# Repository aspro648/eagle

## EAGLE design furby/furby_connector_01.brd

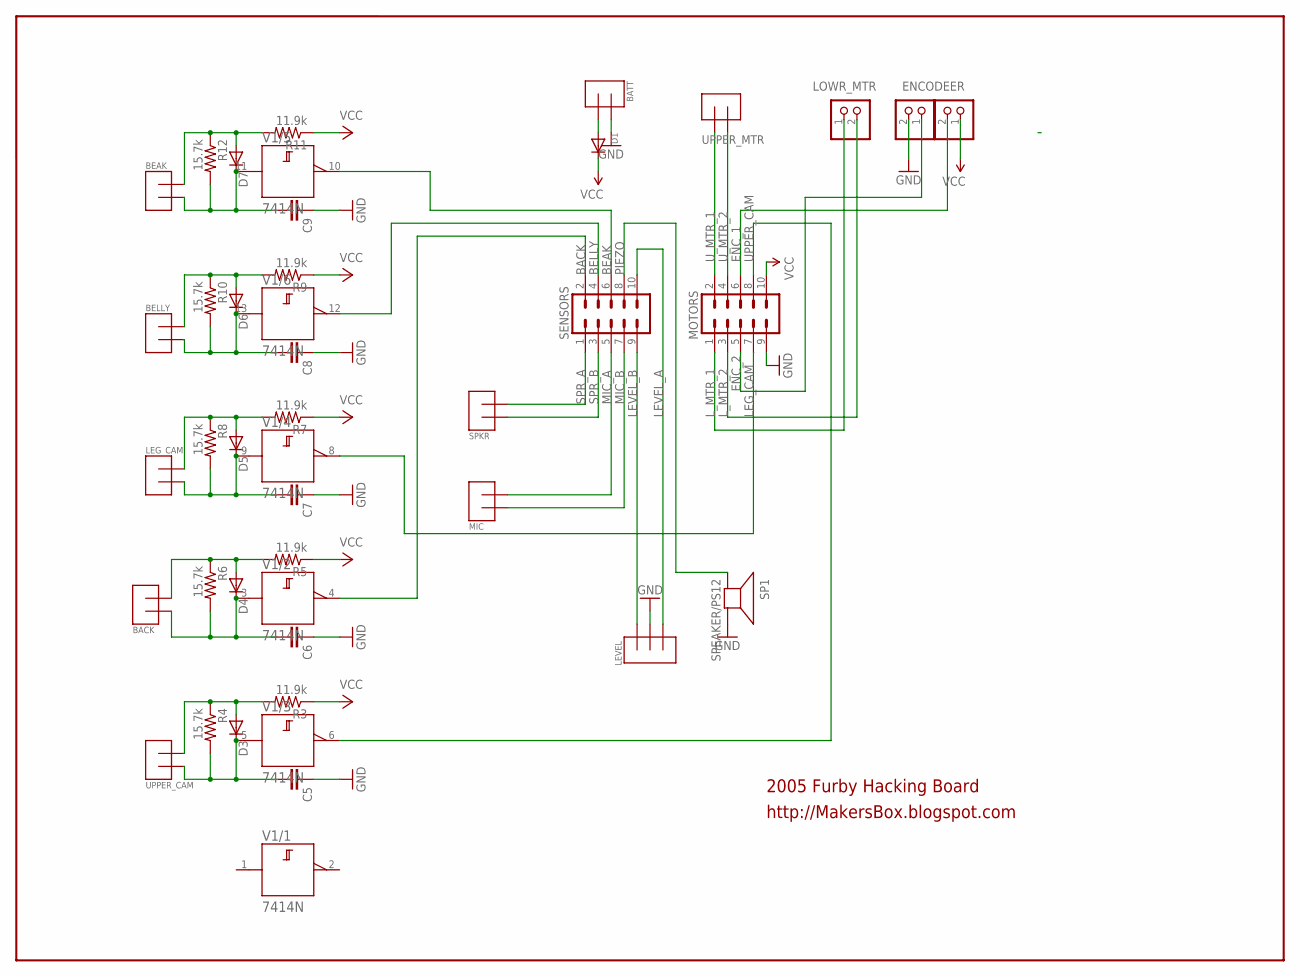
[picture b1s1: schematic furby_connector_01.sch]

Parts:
BACK: TERMINAL2; TERMINAL_2
BATT: TERMINAL2; TERMINAL_2
BEAK: TERMINAL2; TERMINAL_2
BELLY: TERMINAL2; TERMINAL_2
C5, C6, C7, C8, C9: CAPPTH; CAP-PTH-SMALL
D1: DIODEDO-1N4148; DO-1N4148
D3, D4, D5, D6, D7: DIODE-D-2.5; D-2.5
ENCODE2: JST_2PIN-THM; JST-PH-2-THM
ENCODEER: JST_2PIN-THM; JST-PH-2-THM
LEG_CAM: TERMINAL2; TERMINAL_2
LEVEL: TERMINAL; TERMINAL_3
LOWR_MTR: JST_2PIN-THM; JST-PH-2-THM
MIC: TERMINAL2; TERMINAL_2
MOTORS: M05X2SHD; 2X5-SHROUDED
R3, R5, R7, R9, R11: 11.9k; 0204V
R4, R6, R8, R10, R12: 15.7k; 0204V
SENSORS: M05X2SHD; 2X5-SHROUDED
SP1: SPEAKER/PS12; PS12
SPKR: TERMINAL2; TERMINAL_2
UPPER_CAM: TERMINAL2; TERMINAL_2
UPPER_MTR: TERMINAL2; TERMINAL_2
V1: 7414N; DIL14

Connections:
+UB: V1.14 (+UB)
-UB: V1.7 (-UB)
BACK: SENSORS.2, V1.4 (Y)
BEAK: SENSORS.6, V1.10 (Y)
BELLY: SENSORS.4, V1.12 (Y)
ENC_1: ENCODE2.2 (1), MOTORS.6
ENC_2: ENCODEER.1 (2), MOTORS.5
GND: BATT.P$1, C5.1, C6.1, C7.1, C8.1, C9.1, ENCODEER.2 (1), LEVEL.P$2, MOTORS.9, SP1.P$2 (-)
LEG_CAM: MOTORS.7, V1.8 (Y)
LEVEL_A: LEVEL.P$3, SENSORS.10
LEVEL_B: LEVEL.P$1, SENSORS.9
L_MTR_1: LOWR_MTR.1 (2), MOTORS.1
L_MTR_2: LOWR_MTR.2 (1), MOTORS.3
MIC_A: MIC.P$2, SENSORS.5
MIC_B: MIC.P$1, SENSORS.7
unnamed: BATT.P$2, D1.A
unnamed: D3.A, R3.2, R4.1, UPPER_CAM.P$2
unnamed: C5.2, D3.C, R4.2, UPPER_CAM.P$1, V1.5 (A)
unnamed: BACK.P$2, D4.A, R5.2, R6.1
unnamed: BACK.P$1, C6.2, D4.C, R6.2, V1.3 (A)
unnamed: D5.A, LEG_CAM.P$1, R7.2, R8.1
unnamed: C7.2, D5.C, LEG_CAM.P$2, R8.2, V1.9 (A)
unnamed: BELLY.P$1, D6.A, R9.2, R10.1
unnamed: BELLY.P$2, C8.2, D6.C, R10.2, V1.13 (A)
unnamed: BEAK.P$1, D7.A, R11.2, R12.1
unnamed: BEAK.P$2, C9.2, D7.C, R12.2, V1.11 (A)
PIEZO: SENSORS.8, SP1.P$1 (+)
SPR_A: SENSORS.1, SPKR.P$2
SPR_B: SENSORS.3, SPKR.P$1
UPPER_CAM: MOTORS.8, V1.6 (Y)
U_MTR_1: MOTORS.2, UPPER_MTR.P$1
U_MTR_2: MOTORS.4, UPPER_MTR.P$2
VCC: D1.C, ENCODE2.1 (2), MOTORS.10, R3.1, R5.1, R7.1, R9.1, R11.1

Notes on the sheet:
2005 Furby Hacking Board
http://MakersBox.blogspot.com

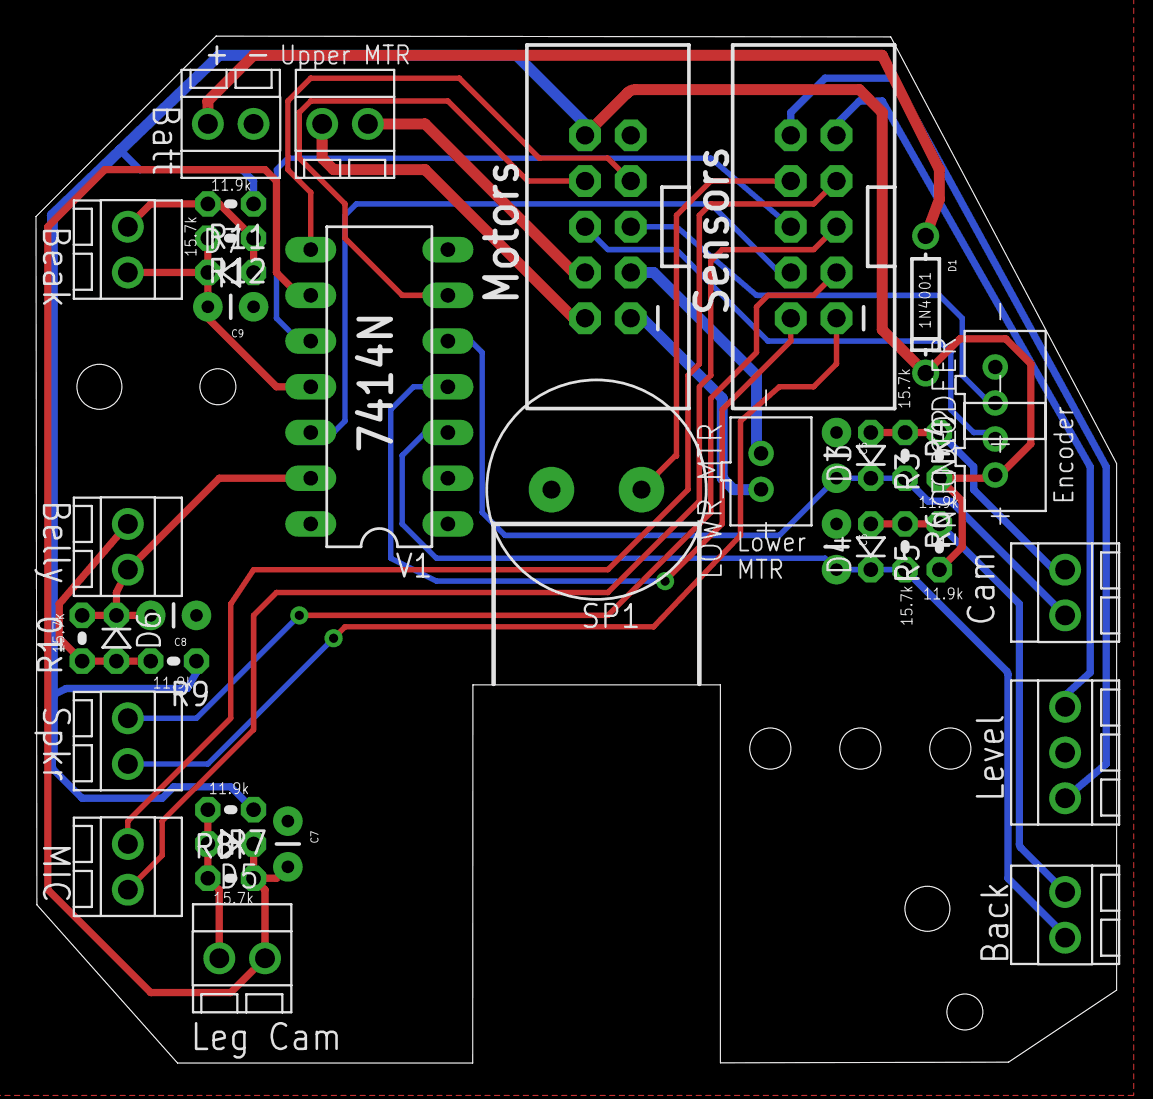
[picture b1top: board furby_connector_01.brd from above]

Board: 2 copper layers, 60.0 x 57.1 mm, 38 parts (0 on the bottom side), 31 nets.

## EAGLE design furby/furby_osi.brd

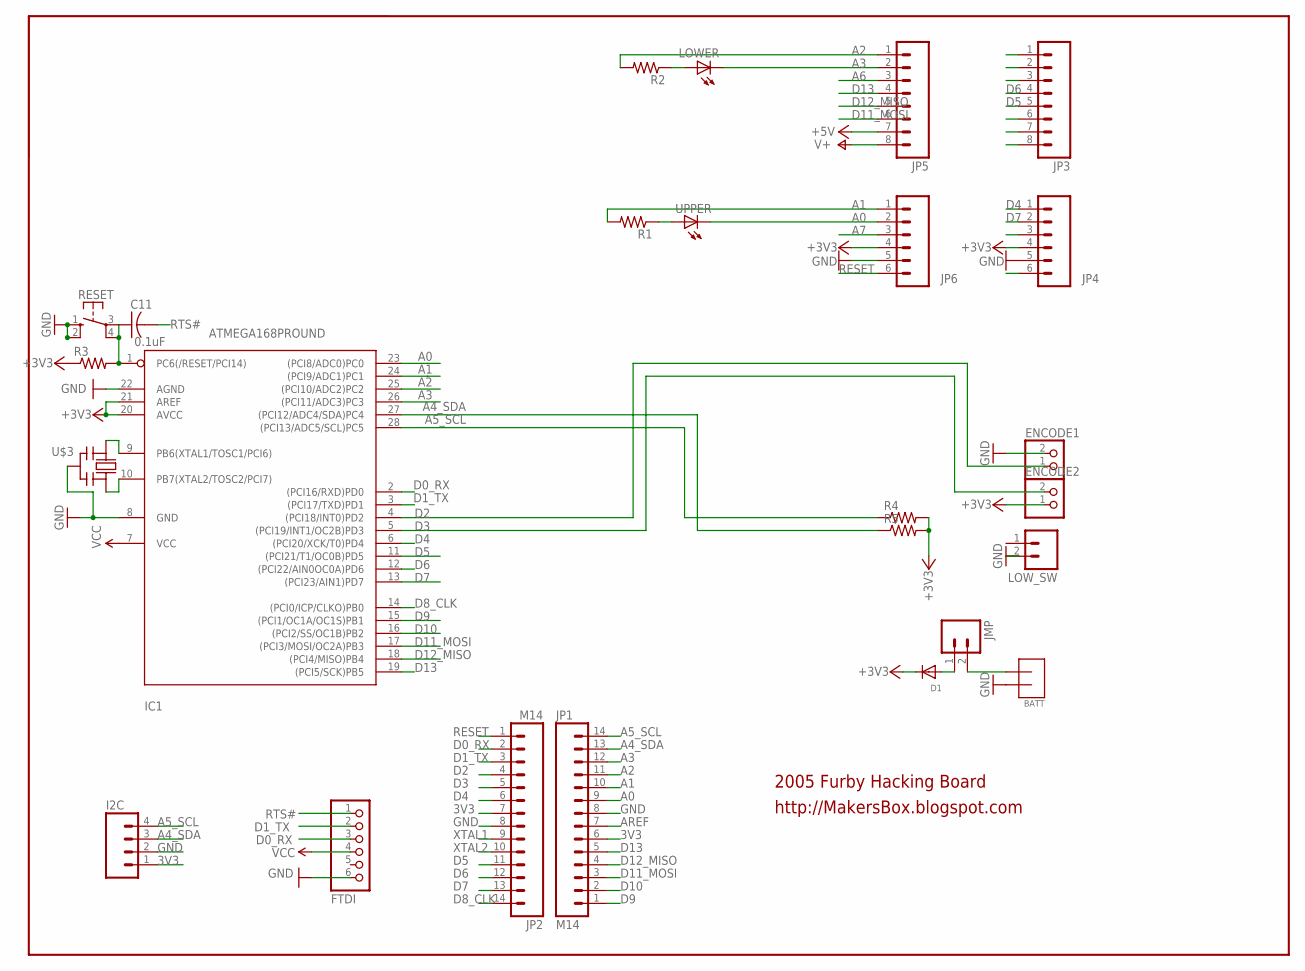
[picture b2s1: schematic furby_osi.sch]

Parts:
BATT: TERMINAL2; TERMINAL_2
C11: 0.1uF; C025-025X050
D1: DIODEDO-1N4148; DO-1N4148
ENCODE1, ENCODE2: JST_2PIN-THM; JST-PH-2-THM
FTDI: FTDI; 1X06-CLEANBIG
I2C: M04PTH; 1X04
IC1: ATMEGA168PROUND; DIL28-3-ROUND
JMP: M02PTH; 1X02
JP1, JP2: M14; 1X14
JP3, JP5: M081X08; 1X08
JP4, JP6: M06SIP; 1X06
LOWER: LED3MM
LOW_SW: M02PTH; 1X02
R1, R2, R3, R4, R5: R-US_0204/7; 0204/7
RESET: 10-XX; B3F-10XX
U$3: CERMOSCILL-THM; CERM_OSC
UPPER: LED3MM

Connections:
3V3: D1.C, ENCODE2.1 (2), FTDI.4, I2C.1, IC1.7 (VCC), IC1.20 (AVCC), IC1.21 (AREF), JP1.6, JP2.7, JP4.4, JP6.4, R3.1, R4.2, R5.2
+5V: JP5.7
A0: IC1.23 ((PCI8/ADC0)PC0), JP1.9, JP6.2, UPPER.K (C)
A1: IC1.24 ((PCI9/ADC1)PC1), JP1.10, JP6.1, R1.2
A2: IC1.25 ((PCI10/ADC2)PC2), JP1.11, JP5.1, R2.2
A3: IC1.26 ((PCI11/ADC3)PC3), JP1.12, JP5.2, LOWER.K (C)
A4_SDA: I2C.3, IC1.27 ((PCI12/ADC4/SDA)PC4), JP1.13, R5.1
A5_SCL: I2C.4, IC1.28 ((PCI13/ADC5/SCL)PC5), JP1.14, R4.1
A6: JP5.3
A7: JP6.3
AREF: JP1.7
D0_RX: FTDI.3, IC1.2 ((PCI16/RXD)PD0), JP2.2
D1_TX: FTDI.2, IC1.3 ((PCI17/TXD)PD1), JP2.3
D2: ENCODE1.1 (2), IC1.4 ((PCI18/INT0)PD2), JP2.4
D3: ENCODE2.2 (1), IC1.5 ((PCI19/INT1/OC2B)PD3), JP2.5
D4: IC1.6 ((PCI20/XCK/T0)PD4), JP2.6, JP4.1
D5: IC1.11 ((PCI21/T1/OC0B)PD5), JP2.11, JP3.5
D6: IC1.12 ((PCI22/AIN0OC0A)PD6), JP2.12, JP3.4
D7: IC1.13 ((PCI23/AIN1)PD7), JP2.13, JP4.2
D8_CLK: IC1.14 ((PCI0/ICP/CLKO)PB0), JP2.14
D9: IC1.15 ((PCI1/OC1A/OC1S)PB1), JP1.1
D10: IC1.16 ((PCI2/SS/OC1B)PB2), JP1.2
D11_MOSI: IC1.17 ((PCI3/MOSI/OC2A)PB3), JP1.3, JP5.6
D12_MISO: IC1.18 ((PCI4/MISO)PB4), JP1.4, JP5.5
D13: IC1.19 ((PCI5/SCK)PB5), JP1.5, JP5.4
GND: BATT.P$1, ENCODE1.2 (1), FTDI.6, I2C.2, IC1.8 (GND), IC1.22 (AGND), JP1.8, JP2.8, JP4.5, JP6.5, LOW_SW.2, RESET.1 (S), RESET.2 (S1), U$3.P$2 (GND)
unnamed: R1.1, UPPER.A
unnamed: LOWER.A, R2.1
unnamed: BATT.P$2, JMP.2
unnamed: D1.A, JMP.1
RESET: C11.1, IC1.1 (PC6(/RESET/PCI14)), JP2.1, JP6.6, R3.2, RESET.3, RESET.4 (P1)
RTS#: C11.2, FTDI.1
V+: JP5.8
XTAL1: IC1.9 (PB6(XTAL1/TOSC1/PCI6)), JP2.9, U$3.P$1 (IN)
XTAL2: IC1.10 (PB7(XTAL2/TOSC2/PCI7)), JP2.10, U$3.P$3 (OUT)

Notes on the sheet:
2005 Furby Hacking Board
http://MakersBox.blogspot.com

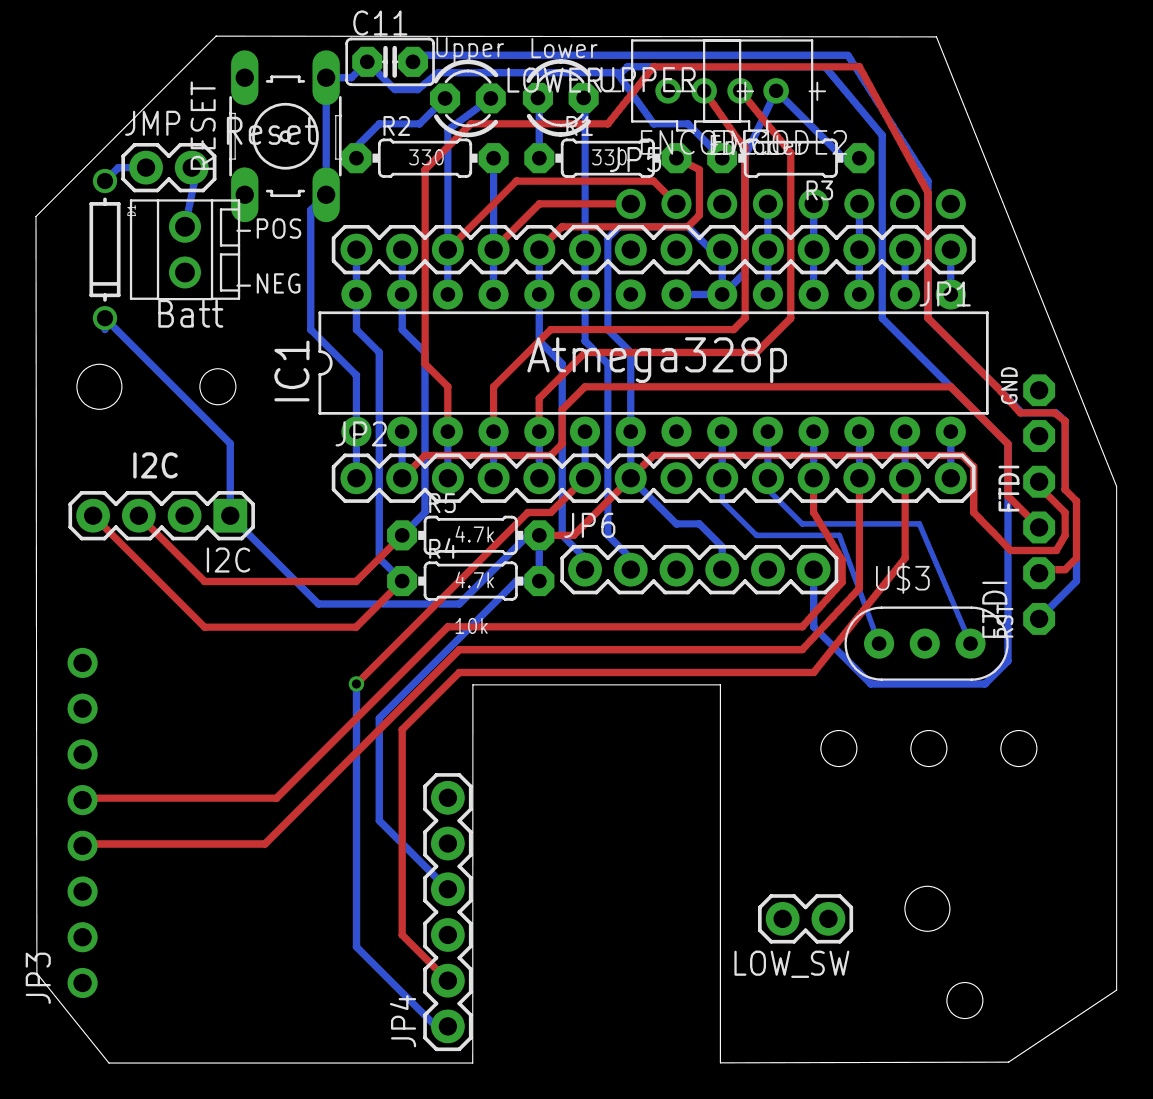
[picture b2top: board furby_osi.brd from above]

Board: 2 copper layers, 60.0 x 57.1 mm, 25 parts (0 on the bottom side), 30 nets.

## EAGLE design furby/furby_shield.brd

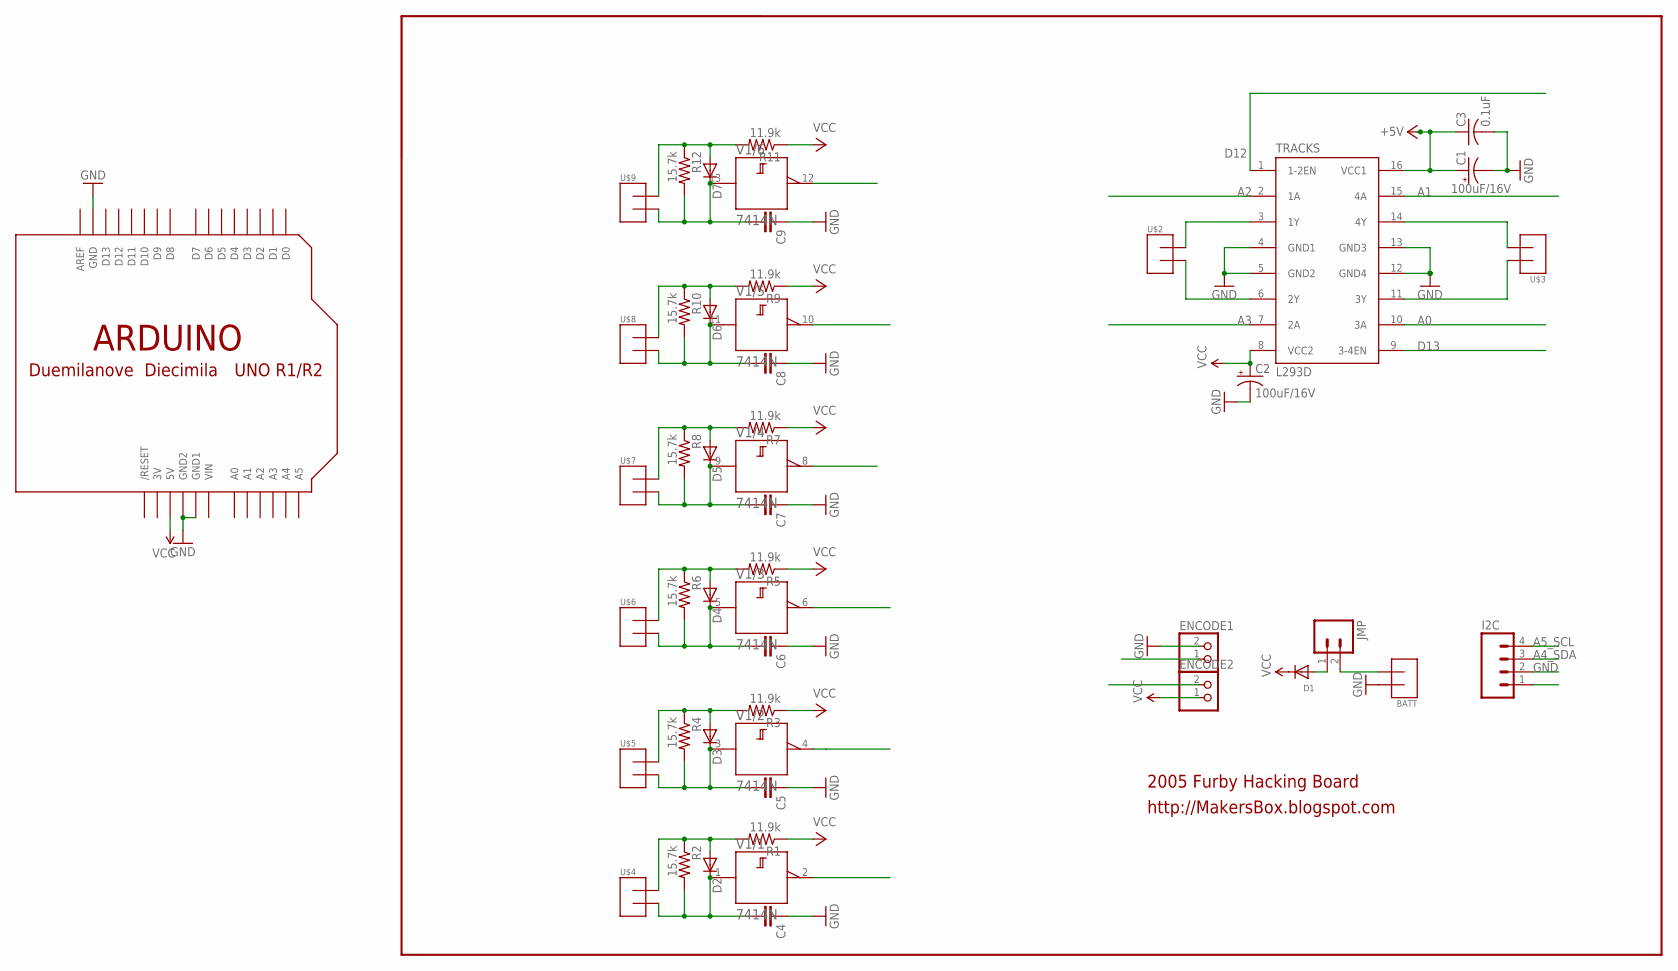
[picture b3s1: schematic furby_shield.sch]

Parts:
BATT: TERMINAL2; TERMINAL_2
C1, C2: 100uF/16V; E2,5-6
C3: 0.1uF; C025-025X050
C4, C5, C6, C7, C8, C9: CAPPTH; CAP-PTH-SMALL
D1: DIODEDO-1N4148; DO-1N4148
D2, D3, D4, D5, D6, D7: DIODE-D-2.5; D-2.5
ENCODE1, ENCODE2: JST_2PIN-THM; JST-PH-2-THM
I2C: M04PTH; 1X04
JMP: M02PTH; 1X02
R1, R3, R5, R7, R9, R11: 11.9k; 0204V
R2, R4, R6, R8, R10, R12: 15.7k; 0204V
TRACKS: L293D; DIL16
U$1: ARDUINO-BPLACE
U$2, U$3, U$4, U$5, U$6, U$7, U$8, U$9: TERMINAL2; TERMINAL_2
V1: 7414N; DIL14

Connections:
3V: U$1.3V
+5V: C1.+, C3.1, TRACKS.16 (VCC1)
+UB: V1.14 (+UB)
-UB: V1.7 (-UB)
A0: TRACKS.10 (3A)
A1: TRACKS.15 (4A)
A2: TRACKS.2 (1A)
A3: TRACKS.7 (2A)
A4: V1.2 (Y)
A4_SDA: I2C.3
A5: V1.8 (Y)
A5_SCL: I2C.4
A6: V1.12 (Y)
D1: V1.4 (Y)
D2: V1.6 (Y)
D3: V1.10 (Y)
D12: TRACKS.1 (1-2EN)
D13: TRACKS.9 (3-4EN)
GND: BATT.P$1, C1.-, C2.-, C3.2, C4.1, C5.1, C6.1, C7.1, C8.1, C9.1, ENCODE1.2 (1), I2C.2, TRACKS.4 (GND1), TRACKS.5 (GND2), TRACKS.12 (GND4), TRACKS.13 (GND3), U$1.GND, U$1.GND1, U$1.GND2
unnamed: BATT.P$2, JMP.2
unnamed: D1.A, JMP.1
unnamed: TRACKS.6 (2Y), U$2.P$2
unnamed: TRACKS.11 (3Y), U$3.P$1
unnamed: TRACKS.14 (4Y), U$3.P$2
unnamed: TRACKS.3 (1Y), U$2.P$1
unnamed: D2.A, R1.2, R2.1, U$4.P$1
unnamed: C4.2, D2.C, R2.2, U$4.P$2, V1.1 (A)
unnamed: D3.A, R3.2, R4.1, U$5.P$1
unnamed: C5.2, D3.C, R4.2, U$5.P$2, V1.3 (A)
unnamed: D4.A, R5.2, R6.1, U$6.P$1
unnamed: C6.2, D4.C, R6.2, U$6.P$2, V1.5 (A)
unnamed: D5.A, R7.2, R8.1, U$7.P$1
unnamed: C7.2, D5.C, R8.2, U$7.P$2, V1.9 (A)
unnamed: D6.A, R9.2, R10.1, U$8.P$1
unnamed: C8.2, D6.C, R10.2, U$8.P$2, V1.11 (A)
unnamed: D7.A, R11.2, R12.1, U$9.P$1
unnamed: C9.2, D7.C, R12.2, U$9.P$2, V1.13 (A)
VCC: C2.+, D1.C, ENCODE2.1 (2), R1.1, R3.1, R5.1, R7.1, R9.1, R11.1, TRACKS.8 (VCC2), U$1.5V
VIN: U$1.VIN

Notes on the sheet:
2005 Furby Hacking Board
http://MakersBox.blogspot.com

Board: 2 copper layers, 44 parts (0 on the bottom side), 21 nets, no tracks yet.

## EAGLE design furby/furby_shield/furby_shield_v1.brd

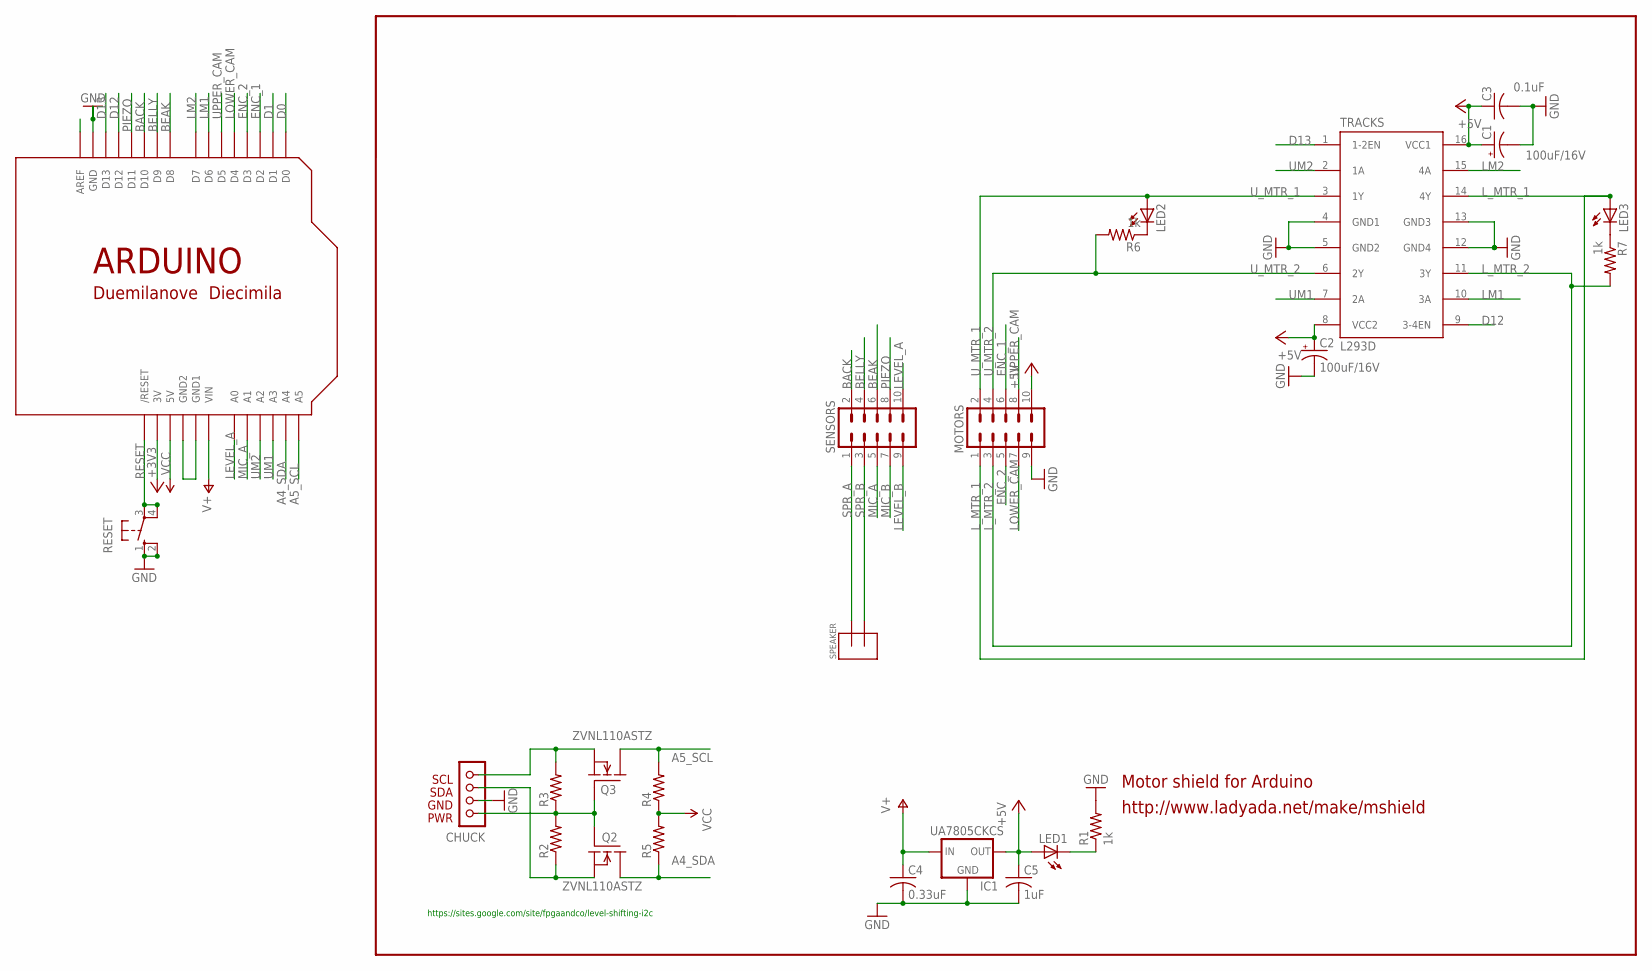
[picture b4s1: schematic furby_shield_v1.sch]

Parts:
C1, C2: 100uF/16V; E2,5-6
C3: 0.1uF; C025-025X050
C4: 0.33uF; C025-024X044
C5: 1uF; C025-024X044
CHUCK: NUNCHUCK; CONN
IC1: UA7805CKCS; TO-220-ALT
LED1, LED2, LED3: LED3MM
MOTORS: M05X2SHD; 2X5-SHROUDED
Q2, Q3: ZVNL110ASTZ; TO92-INLINE
R1, R6, R7: 1k; 0204/5
R2, R3, R4, R5: R-US_0204/7; 0204/7
RESET: 10-XX; B3F-10XX
SENSORS: M05X2SHD; 2X5-SHROUDED
SPEAKER: TERMINAL2; TERMINAL_2
TRACKS: L293D; DIL16
U$1: ARDUINO-NOHOLE

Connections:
+3V3: CHUCK.PWR, Q2.2 (G), Q3.2 (G), R2.2, R3.1, U$1.3V
+5V: C1.+, C2.+, C3.1, C5.1, IC1.OUT, LED1.A, MOTORS.10, TRACKS.8 (VCC2), TRACKS.16 (VCC1)
A4_SDA: Q2.1 (D), R5.1, U$1.A4
A5_SCL: Q3.1 (D), R4.2, U$1.A5
BACK: SENSORS.2, U$1.D10
BEAK: SENSORS.6, U$1.D8
BELLY: SENSORS.4, U$1.D9
D0: U$1.D0
D1: U$1.D1
D12: TRACKS.9 (3-4EN), U$1.D12
D13: TRACKS.1 (1-2EN), U$1.D13
ENC_1: MOTORS.6, U$1.D2
ENC_2: MOTORS.5, U$1.D3
GND: C1.-, C2.-, C3.2, C4.2, C5.2, CHUCK.GND, IC1.GND, MOTORS.9, R1.2, RESET.1 (S), RESET.2 (S1), TRACKS.4 (GND1), TRACKS.5 (GND2), TRACKS.12 (GND4), TRACKS.13 (GND3), U$1.GND, U$1.GND1, U$1.GND2
LEVEL_A: SENSORS.10, U$1.A0
LEVEL_B: SENSORS.9
LM1: TRACKS.10 (3A), U$1.D6
LM2: TRACKS.15 (4A), U$1.D7
LOWER_CAM: MOTORS.7, U$1.D4
L_MTR_1: LED3.A, MOTORS.1, TRACKS.14 (4Y)
L_MTR_2: MOTORS.3, R7.2, TRACKS.11 (3Y)
MIC_A: SENSORS.5, U$1.A1
MIC_B: SENSORS.7
unnamed: LED2.K (C), R6.1
unnamed: LED1.K (C), R1.1
unnamed: LED3.K (C), R7.1
PIEZO: SENSORS.8, U$1.D11
RESET: RESET.3, RESET.4 (P1), U$1.RESET (/RESET)
SCL: CHUCK.SCL, Q3.3 (S), R3.2
SDA: CHUCK.SDA, Q2.3 (S), R2.1
SPR_A: SENSORS.1, SPEAKER.P$1
SPR_B: SENSORS.3, SPEAKER.P$2
UM1: TRACKS.7 (2A), U$1.A3
UM2: TRACKS.2 (1A), U$1.A2
UPPER_CAM: MOTORS.8, U$1.D5
U_MTR_1: LED2.A, MOTORS.2, TRACKS.3 (1Y)
U_MTR_2: MOTORS.4, R6.2, TRACKS.6 (2Y)
V+: C4.1, IC1.IN, U$1.VIN
VCC: R4.1, R5.2, U$1.5V, U$1.AREF

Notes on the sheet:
Motor shield for Arduino
http://www.ladyada.net/make/mshield
https://sites.google.com/site/fpgaandco/level-shifting-i2c

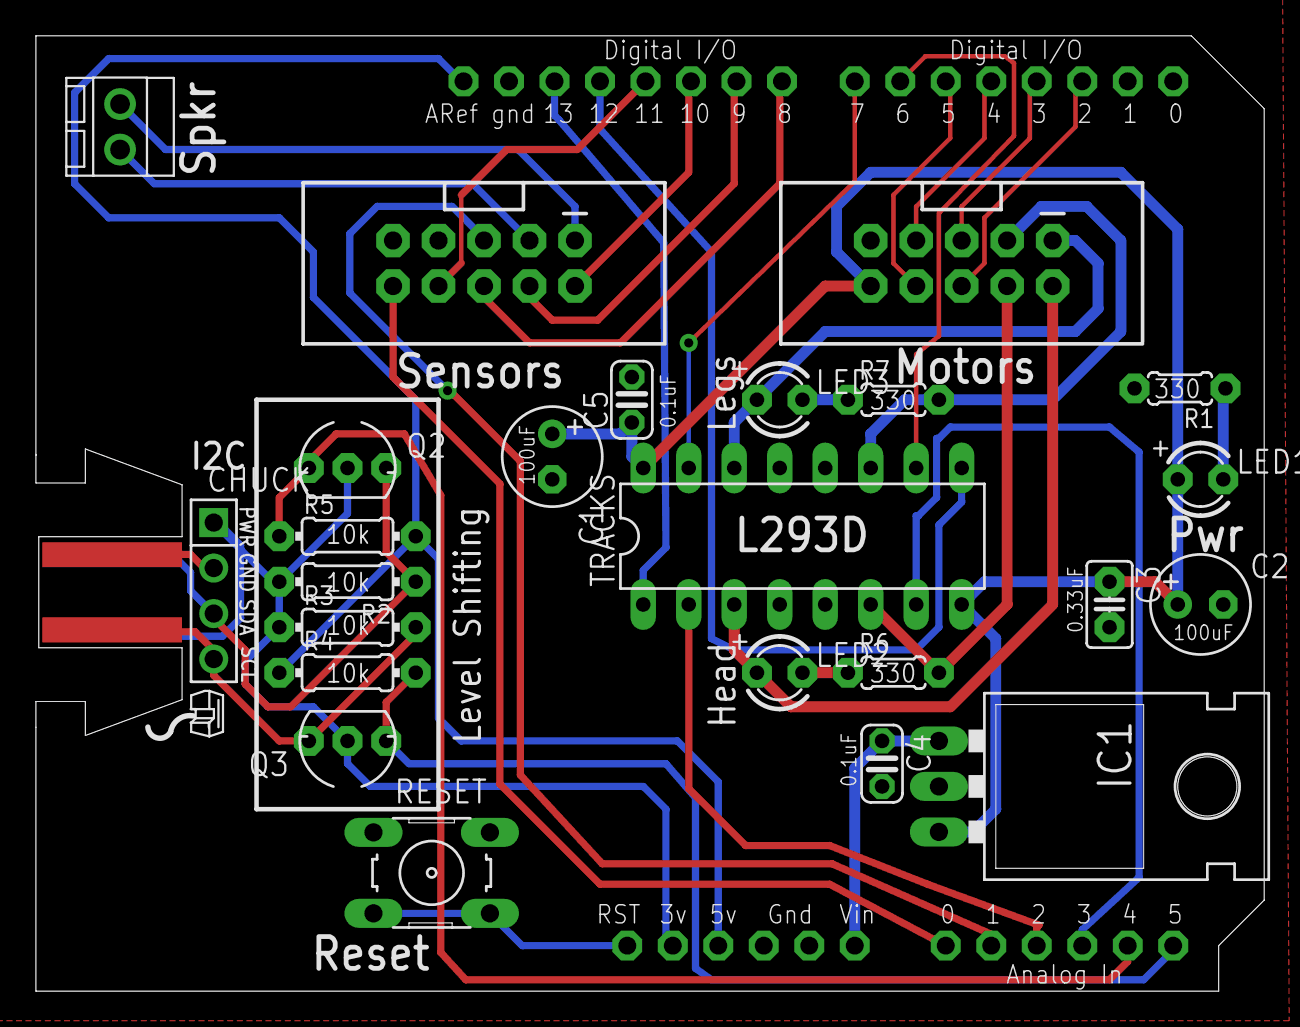
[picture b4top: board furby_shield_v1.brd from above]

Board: 2 copper layers, 68.6 x 53.3 mm, 25 parts (0 on the bottom side), 35 nets.

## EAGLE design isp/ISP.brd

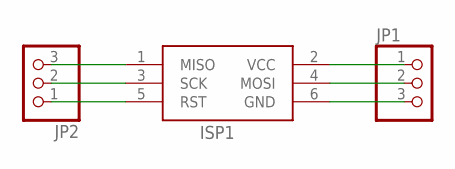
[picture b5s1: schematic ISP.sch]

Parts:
ISP1: AVRISP-6; AVRISP
JP1, JP2: PINHD-1X3; 1X03

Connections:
unnamed: ISP1.2 (VCC), JP1.1
unnamed: ISP1.4 (MOSI), JP1.2
unnamed: ISP1.6 (GND), JP1.3
unnamed: ISP1.5 (RST), JP2.1
unnamed: ISP1.3 (SCK), JP2.2
unnamed: ISP1.1 (MISO), JP2.3

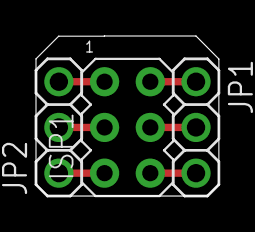
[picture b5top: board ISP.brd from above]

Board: 2 copper layers, 10.2 x 8.9 mm, 3 parts (0 on the bottom side), 6 nets.

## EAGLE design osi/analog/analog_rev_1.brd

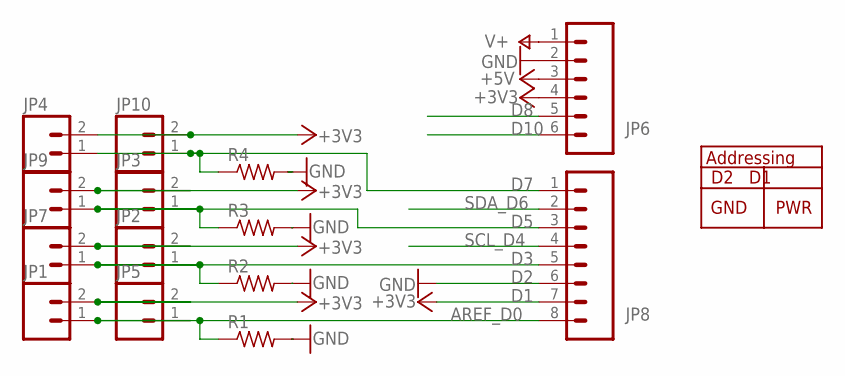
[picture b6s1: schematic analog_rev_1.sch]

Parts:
JP1, JP2, JP3, JP4, JP5, JP7, JP9, JP10: M02PTH; 1X02
JP6: M06SIP; 1X06
JP8: M081X08; 1X08
R1, R2, R3, R4: R-US_0204/7; 0204/7

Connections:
+5V: JP6.3
AREF_D0: JP1.1, JP5.1, JP8.8, R1.1
D1: JP1.2, JP2.2, JP3.2, JP4.2, JP5.2, JP6.4, JP7.2, JP8.7, JP9.2, JP10.2
D2: JP8.6
D3: JP2.1, JP7.1, JP8.5, R2.1
D5: JP3.1, JP8.3, JP9.1, R3.1
D7: JP4.1, JP8.1, JP10.1, R4.1
D8: JP6.5
D10: JP6.6
GND: JP6.2, R1.2, R2.2, R3.2, R4.2
SCL_D4: JP8.4
SDA_D6: JP8.2
V+: JP6.1

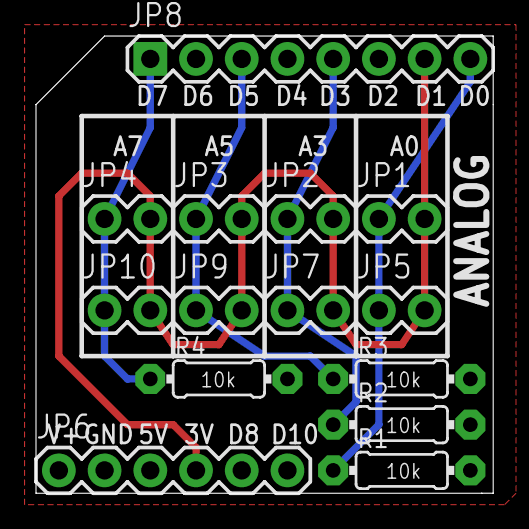
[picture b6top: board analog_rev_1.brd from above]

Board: 2 copper layers, 25.4 x 25.4 mm, 14 parts (0 on the bottom side), 6 nets.

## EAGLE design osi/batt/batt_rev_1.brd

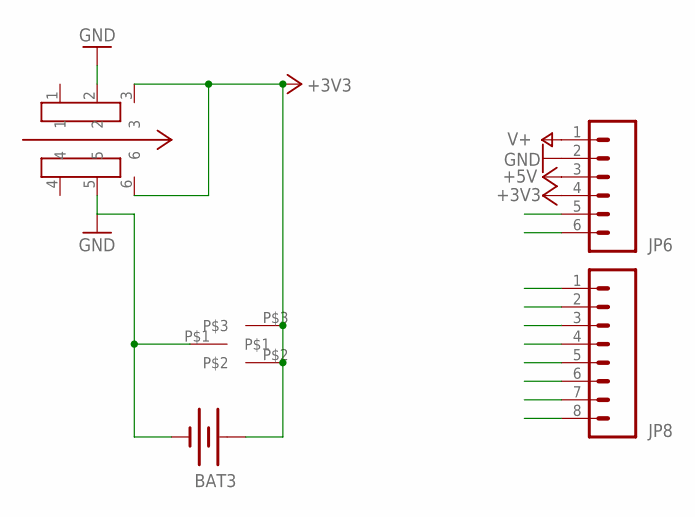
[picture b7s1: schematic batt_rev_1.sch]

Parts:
BAT3: BATTERY20PTH; BATTCOM_20MM_PTH
JP6: 6; 1X06
JP8: 8; 1X08
U$1: SWITCH
U$2: BATT_2032

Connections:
+3V3: BAT3.1 (+), JP6.4, U$1.3, U$1.6, U$2.P$2, U$2.P$3
+5V: JP6.3
AREF_D0: JP8.8
D1: JP8.7
D2: JP8.6
D3: JP8.5
D5: JP8.3
D7: JP8.1
D8: JP6.5
D9: JP6.6
GND: BAT3.2 (-), JP6.2, U$1.2, U$1.5, U$2.P$1
SCL_D4: JP8.4
SDA_D6: JP8.2
V+: JP6.1

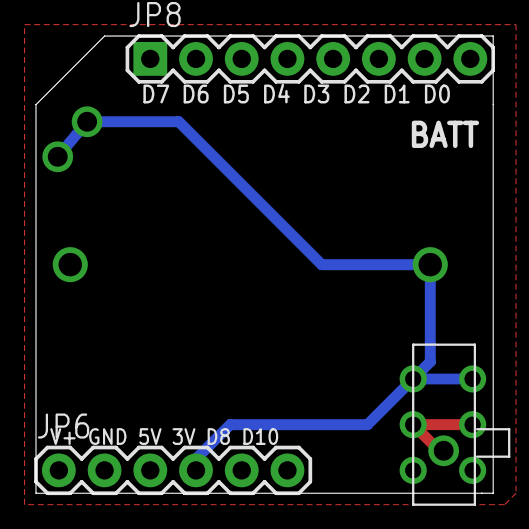
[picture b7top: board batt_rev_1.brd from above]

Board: 2 copper layers, 25.4 x 25.4 mm, 5 parts (0 on the bottom side), 2 nets.

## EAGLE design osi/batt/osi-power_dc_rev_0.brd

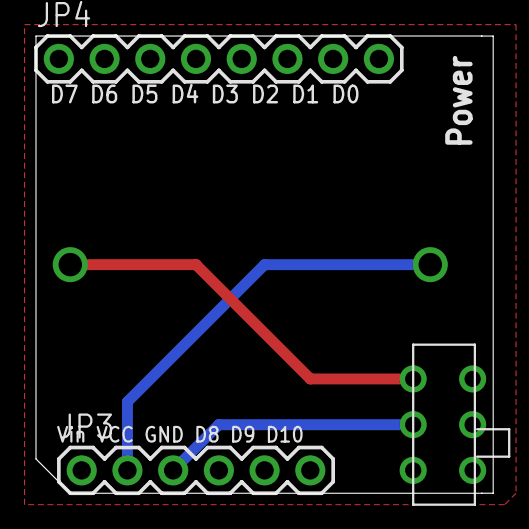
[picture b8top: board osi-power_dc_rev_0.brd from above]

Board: 2 copper layers, 25.4 x 25.4 mm, 4 parts (0 on the bottom side), 3 nets.

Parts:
BAT: BATTCOM_20MM_PTH
JP3: 1X06
JP4: 1X08
U$1: SWITCH

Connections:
GND: JP3.3, U$1.2
unnamed: BAT.2, U$1.3
VCC: BAT.1, JP3.2

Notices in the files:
parts and their libraries:
SparkFun: Licensing: CC v3.0 Share-Alike You are welcome to use this library for commercial purposes.
